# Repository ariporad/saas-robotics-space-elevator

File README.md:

# Space Elevator

This is the code for the SAAS Robotics space elevator robot. It's written in Python 3, and only runs
on a raspberry pi. (It's only been tested on the RPi3).

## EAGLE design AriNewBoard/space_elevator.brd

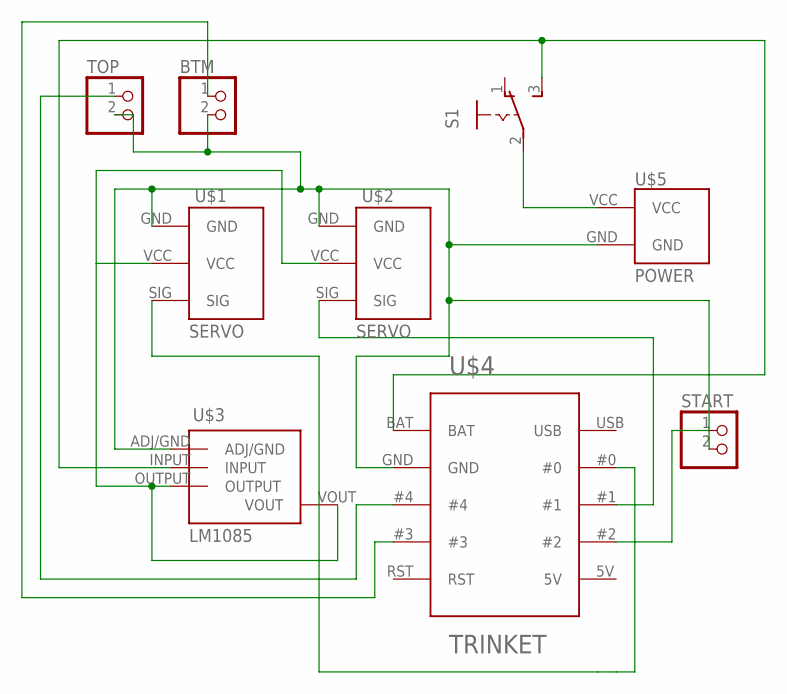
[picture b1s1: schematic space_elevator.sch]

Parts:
BTM: PINHD-1X2; 1X02
S1: 255SB
START: PINHD-1X2; 1X02
TOP: PINHD-1X2; 1X02
U$1, U$2: SERVO
U$3: LM1085; TO220H
U$4: TRINKET; TRINKETUSB
U$5: POWER

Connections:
GND: BTM.2, START.2, TOP.2, U$1.GND, U$2.GND, U$3.ADJ/GND, U$4.GND, U$5.GND
unnamed: S1.2, U$5.VCC
unnamed: S1.3 (S), U$3.INPUT, U$4.BAT
unnamed: U$1.VCC, U$2.VCC, U$3.OUTPUT, U$3.VOUT
unnamed: TOP.1, U$4.#4
unnamed: BTM.1, U$4.#3
unnamed: START.1, U$4.#2
unnamed: U$2.SIG, U$4.#1
unnamed: U$1.SIG, U$4.#0

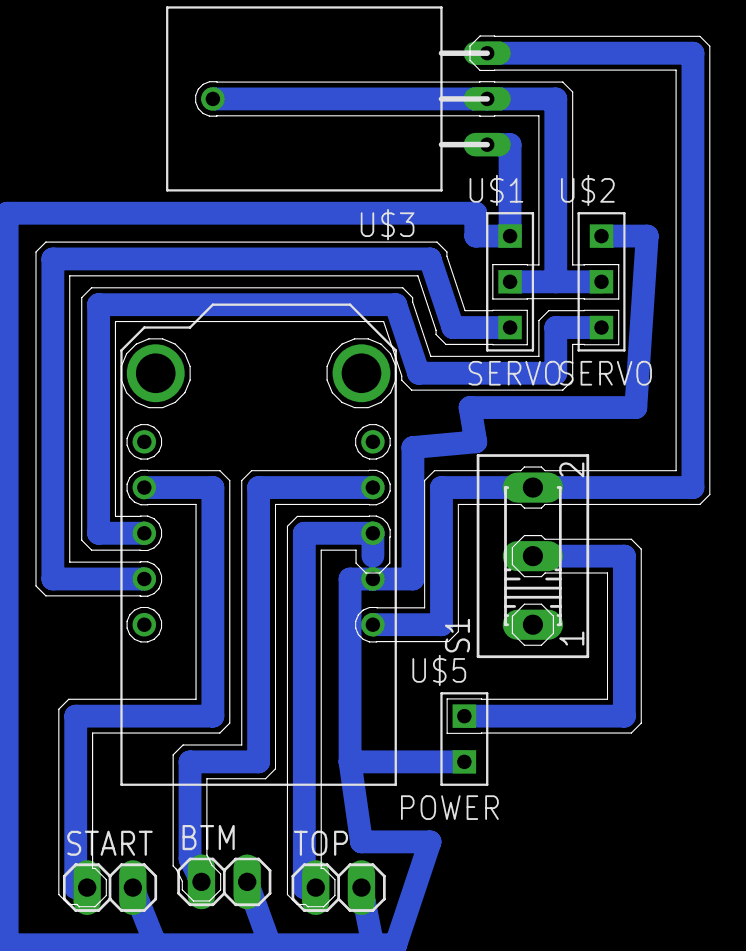
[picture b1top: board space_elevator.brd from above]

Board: 2 copper layers, 37.4 x 48.4 mm, 9 parts (0 on the bottom side), 9 nets.

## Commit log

2016-08-02 feat: switch to arduino
    RPi's are unsuitable for realtime work, as Python might be garbage collecting when you hit something.
2016-08-15 Adafruit Trinket program and EagleCAD files
2016-08-18 Working Momentary Switch for Servo Direction
2016-08-18 Fixed Debounce Bug, added Starting Pull, tested
